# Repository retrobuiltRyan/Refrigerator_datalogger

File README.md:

What happens to your refrigerator temperature when you open the door? When you leave the door open? I built a data-logging device and stuck it in my fridge for a few hours to find out. I have no idea why I spent a weekend doing this.
Arduino logs temp and humidity data to a microSD card. Use exel to graph and plot data. A photosensor confirms the fridge light if you open the door. Sample graph of data is shown. The old fridge form this experience has a wide temp swing. Not a great fridge, ( came with the rental).

https://youtu.be/RkxqKmEyWRI

PCB (Arduino Uno shield) too! Note the i2c pwr lables have a text error on the silkscreen. (oops)

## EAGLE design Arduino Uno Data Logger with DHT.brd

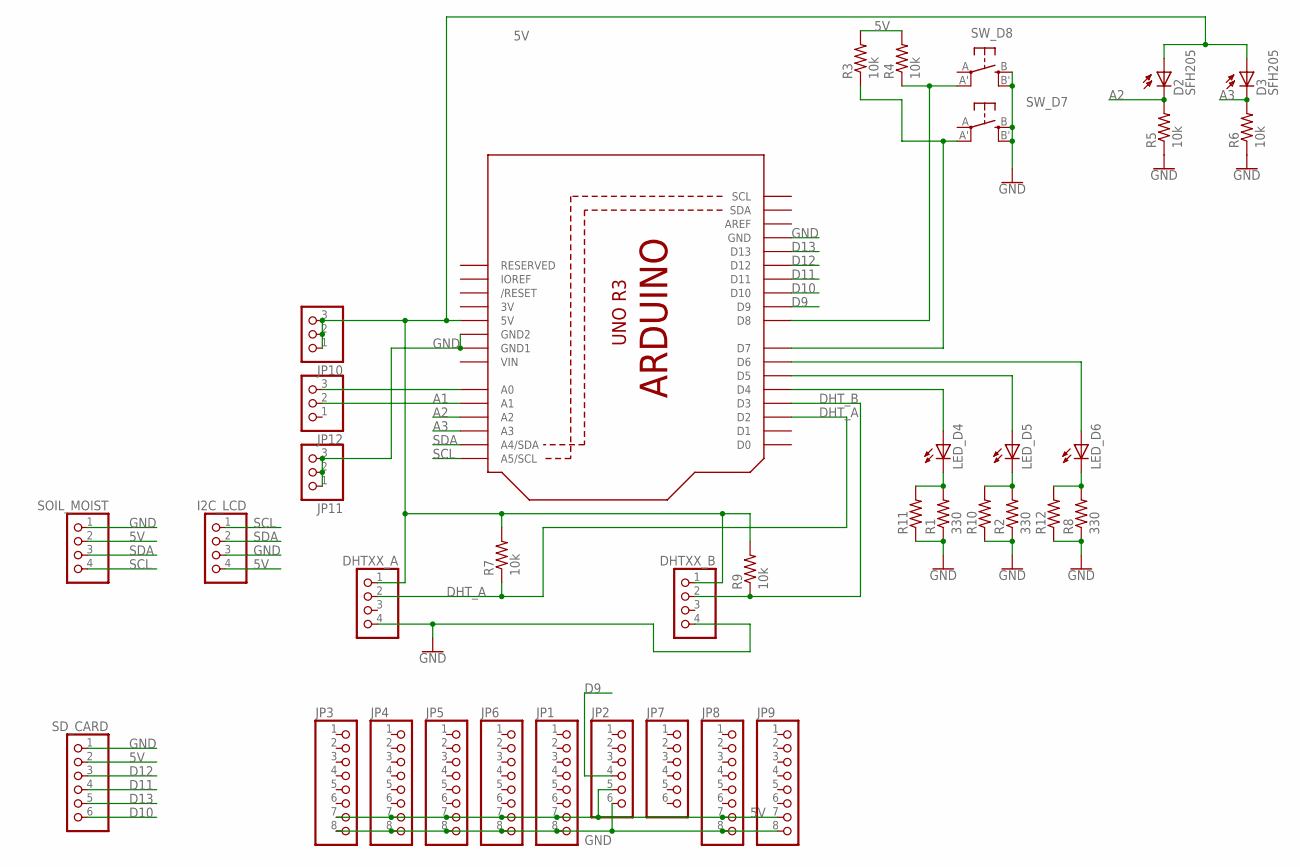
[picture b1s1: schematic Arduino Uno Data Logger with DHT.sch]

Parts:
D2, D3: SFH205
DHTXX_A: PINHD-1X4; 1X04
DHTXX_B: PINHD-1X4; 1X04
I2C_LCD: PINHD-1X4; 1X04
JP1, JP3, JP4, JP5, JP6, JP8, JP9: PINHD-1X8CLEANBIG; 1X08-CLEANBIG
JP2, JP7: PINHD-1X6CB; 1X06-CLEANBIG
JP10, JP11, JP12: PINHD-1X3CB; 1X03-CLEANBIG
LED_D4, LED_D5, LED_D6: LED5MM
R1, R2, R8: 330; 0207/10
R3, R4, R5, R6, R7, R9: 10k; 0207/10
R10, R11, R12: R-US_R2010; R2010
SD_CARD: PINHD-1X6; 1X06
SOIL_MOIST: PINHD-1X4; 1X04
SW_D7, SW_D8: SPST_TACT-EVQQ2; EVQ-Q2
U1: ARDUINOR3-DIMENSION; ARDUINOR3

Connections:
3V: U1.3V
5V: D2.A, D3.A, DHTXX_A.1, DHTXX_B.1, I2C_LCD.4, JP1.7, JP2.5, JP3.7, JP4.7, JP5.7, JP6.7, JP8.7, JP9.7, JP10.1, JP10.2, JP10.3, R3.2, R4.2, R7.2, R9.2, SD_CARD.2, SOIL_MOIST.2, U1.5V
A1: JP12.2, U1.A1
A2: D2.K (C), R5.2, U1.A2
A3: D3.K (C), R6.2, U1.A3
D9: JP2.4, U1.D9
D10: SD_CARD.6, U1.D10
D11: SD_CARD.4, U1.D11
D12: SD_CARD.3, U1.D12
D13: SD_CARD.5, U1.D13
DHT_A: DHTXX_A.2, R7.1, U1.D2
DHT_B: DHTXX_B.2, R9.1, U1.D3
GND: DHTXX_A.4, DHTXX_B.4, I2C_LCD.3, JP1.8, JP2.6, JP3.8, JP4.8, JP5.8, JP6.8, JP8.8, JP9.8, JP11.1, JP11.2, JP11.3, R1.1, R2.1, R5.1, R6.1, R8.1, R10.1, R11.1, R12.1, SD_CARD.1, SOIL_MOIST.1, SW_D7.B (S), SW_D7.B' (S1), SW_D8.B (S), SW_D8.B' (S1), U1.GND, U1.GND1, U1.GND2
unnamed: R4.1, SW_D8.A' (P1), U1.D8
unnamed: R3.1, SW_D7.A' (P1), U1.D7
unnamed: LED_D5.K (C), R2.2, R10.2
unnamed: LED_D4.A, U1.D4
unnamed: LED_D4.K (C), R1.2, R11.2
unnamed: LED_D5.A, U1.D5
unnamed: LED_D6.A, U1.D6
unnamed: LED_D6.K (C), R8.2, R12.2
unnamed: JP12.3, U1.A0
SCL: I2C_LCD.1, SOIL_MOIST.4, U1.A5 (A5/SCL)
SDA: I2C_LCD.2, SOIL_MOIST.3, U1.A4 (A4/SDA)
VIN: U1.VIN

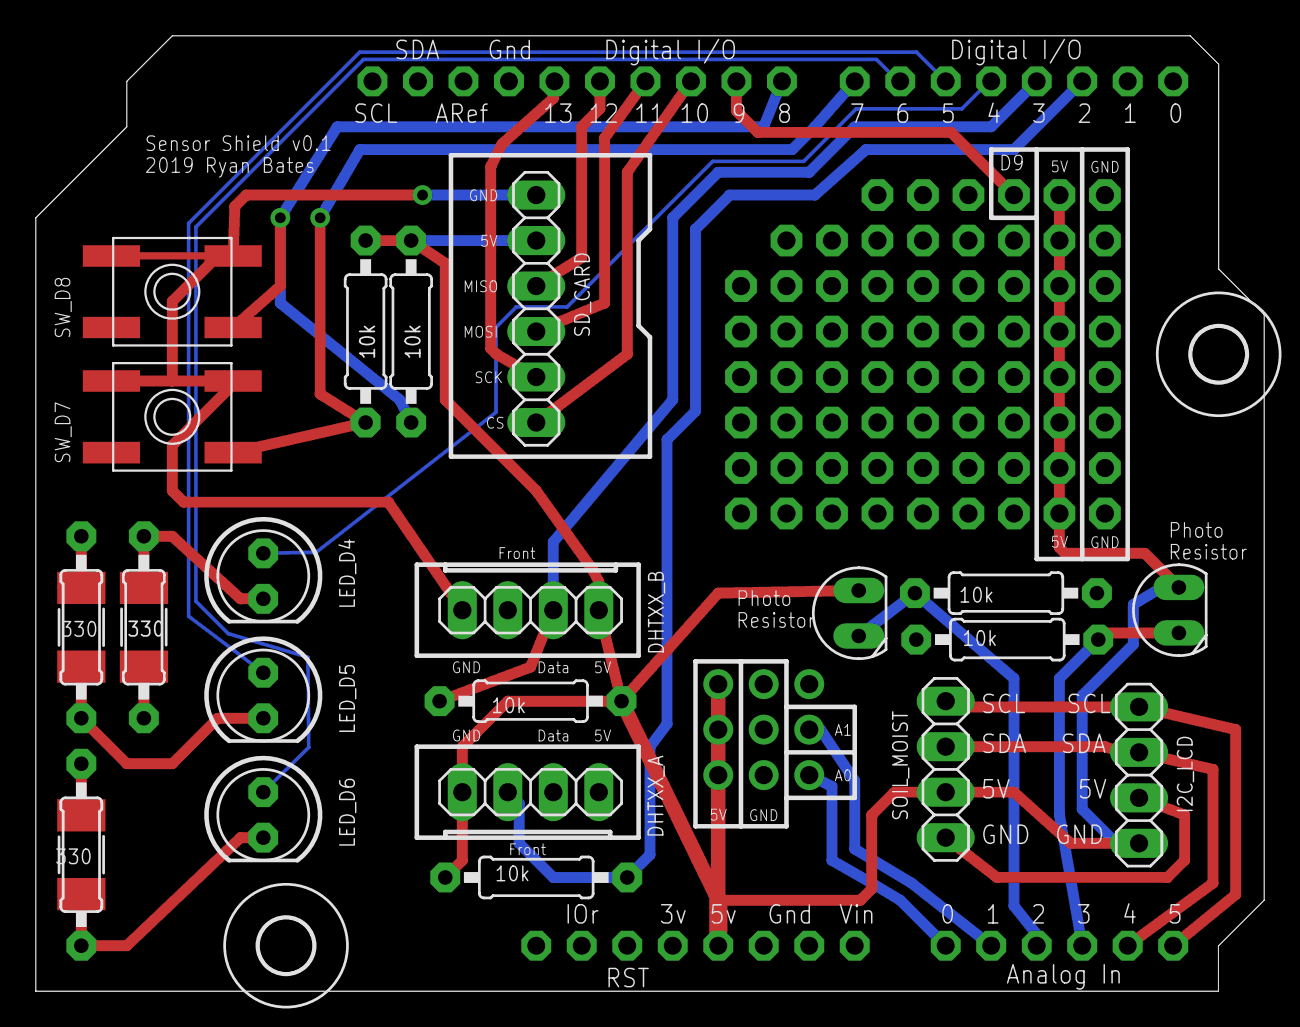
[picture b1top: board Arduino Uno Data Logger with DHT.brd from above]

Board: 2 copper layers, 68.6 x 53.3 mm, 39 parts (0 on the bottom side), 23 nets.

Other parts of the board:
U$1, U$3: 3,0

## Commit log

2025-05-28 Arduino code
2025-05-28 eagle design files
    this is an old project, i would say it might contain an error that i forgot about.

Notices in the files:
parts and their libraries:
SparkFun-PowerSymbols: Licensing: Creative Commons ShareAlike 4.0 International - https://creativecommons.org/licenses/by-sa/4.0
